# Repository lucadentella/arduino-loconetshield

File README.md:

# Loconet Shield / Interface

## Description
Interface to connect a 5V microcontroller to the Loconet bus.
Available as an Arduino shield or a stand-alone module.
A "master" version is also available, which implements power supply and bus termination.

*Interfaccia per collegare un microcontrollore a 5V al bus Loconet.
Disponibile sia come shield per Arduino che come modulo stand-alone.
E' disponibile anche una versione "master", che aggiunge le funzionalità di alimentazione e terminazione del bus.*
## Examples

In the Arduino folder, some basic sketches are provided to demonstrate the use of the interface. The [mrrwa/LocoNet](https://github.com/mrrwa/LocoNet) library is required (can be installed via Library Manager).

*Nella cartella Arduino, sono disponibili alcuni semplici sketch per dimostrare il funzionamento della interfaccia. E' richiesta la libreria [mrrwa/LocoNet](https://github.com/mrrwa/LocoNet) (può essere installata da Library Manager).*

## Documentation
- [Basic tutorial in  **English**](https://youtu.be/1dmCtpfb8J8)  (Youtube)
- [Tutorial base in  **Italiano**](https://youtu.be/m1i-pzcgra8)  (Youtube)
- [MasterInterface+Locobuffer tutorial in  **English**](https://youtu.be/BdRhHBKUpPE)  (Youtube)
- [Tutorial su InterfacciaMaster+Locobuffer in  **Italiano**](https://youtu.be/tLN5pXX8Gf4)  (Youtube)

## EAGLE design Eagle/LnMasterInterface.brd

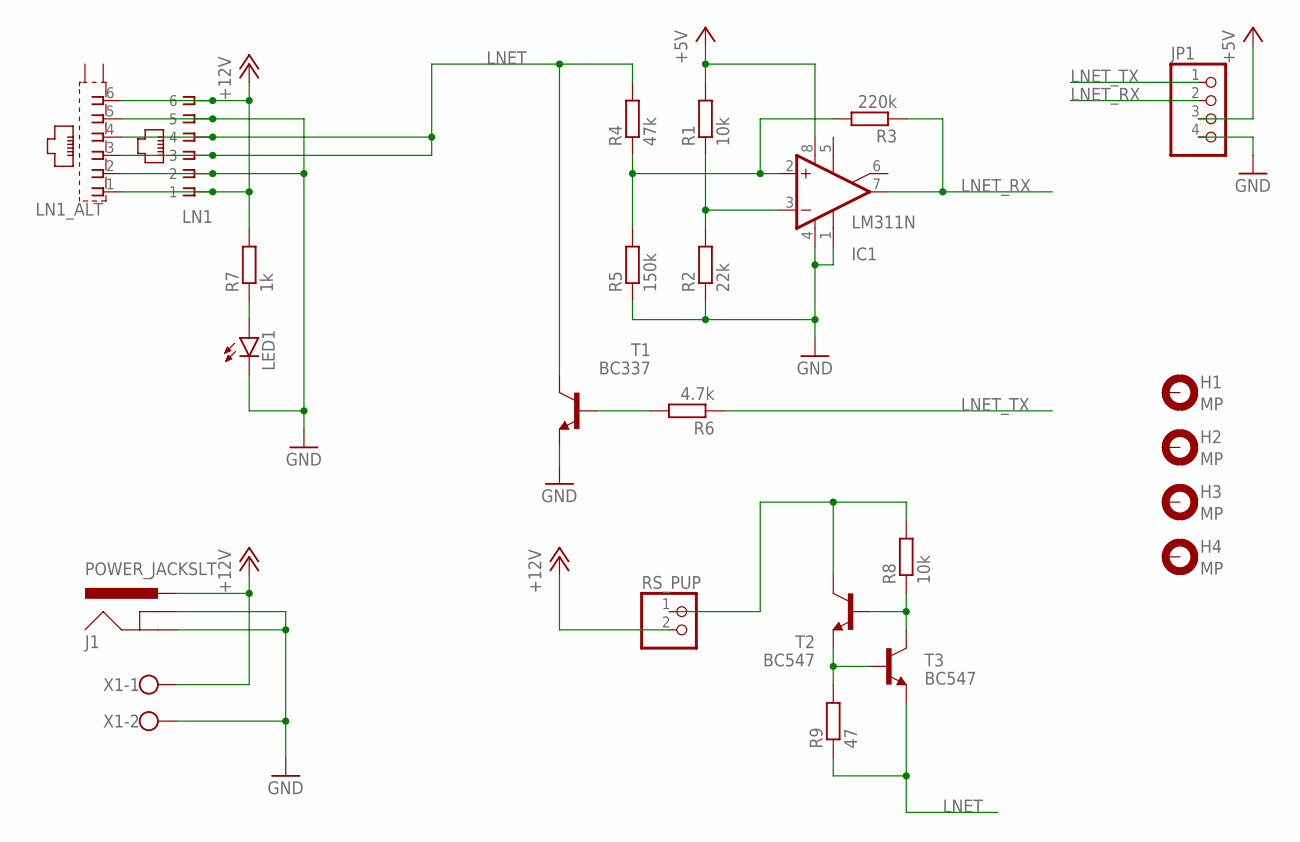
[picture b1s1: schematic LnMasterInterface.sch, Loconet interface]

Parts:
H1, H2, H3, H4: MP; 3,0-PAD
IC1: LM311N; DIL08
J1: POWER_JACKSLT; POWER_JACK_SLOT
JP1: PINHD-1X4; 1X04
LED1: LED3MM
LN1: RJ11-6X; RJ11-NO_SHIELD
LN1_ALT: YH-55-10
R1, R8: 10k; 0207/2V
R2: 22k; 0207/2V
R3: 220k; 0207/2V
R4: 47k; 0207/2V
R5: 150k; 0207/2V
R6: 4.7k; 0207/2V
R7: 1k; 0207/2V
R9: 47; 0207/2V
RS_PUP: PINHD-1X2; 1X02
T1: BC337; TO92
T2, T3: BC547; TO92
X1: W237-102

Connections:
+5V: IC1.8 (V+), JP1.3, R1.2
+12V: J1.PWR, LN1.1, LN1.6, LN1_ALT.1, LN1_ALT.6, R7.2, RS_PUP.2, X1.1
GND: IC1.1 (GND), IC1.4 (V-), J1.GND@1 (GNDBREAK), J1.GND@2 (GND), JP1.4, LED1.K (C), LN1.2, LN1.5, LN1_ALT.2, LN1_ALT.5, R2.1, R5.1, T1.1 (E), X1.2
LNET: LN1.3, LN1.4, LN1_ALT.3, LN1_ALT.4, R4.2, R9.1, T1.3 (C), T3.1 (E)
LNET_RX: IC1.7 (OUT), JP1.2, R3.1
LNET_TX: JP1.1, R6.1
unnamed: R6.2, T1.2 (B)
unnamed: LED1.A, R7.1
unnamed: IC1.3 (-IN), R1.1, R2.2
unnamed: IC1.2 (+IN), R3.2, R4.1, R5.2
unnamed: R9.2, T2.1 (E), T3.2 (B)
unnamed: R8.1, T2.2 (B), T3.3 (C)
unnamed: R8.2, RS_PUP.1, T2.3 (C)

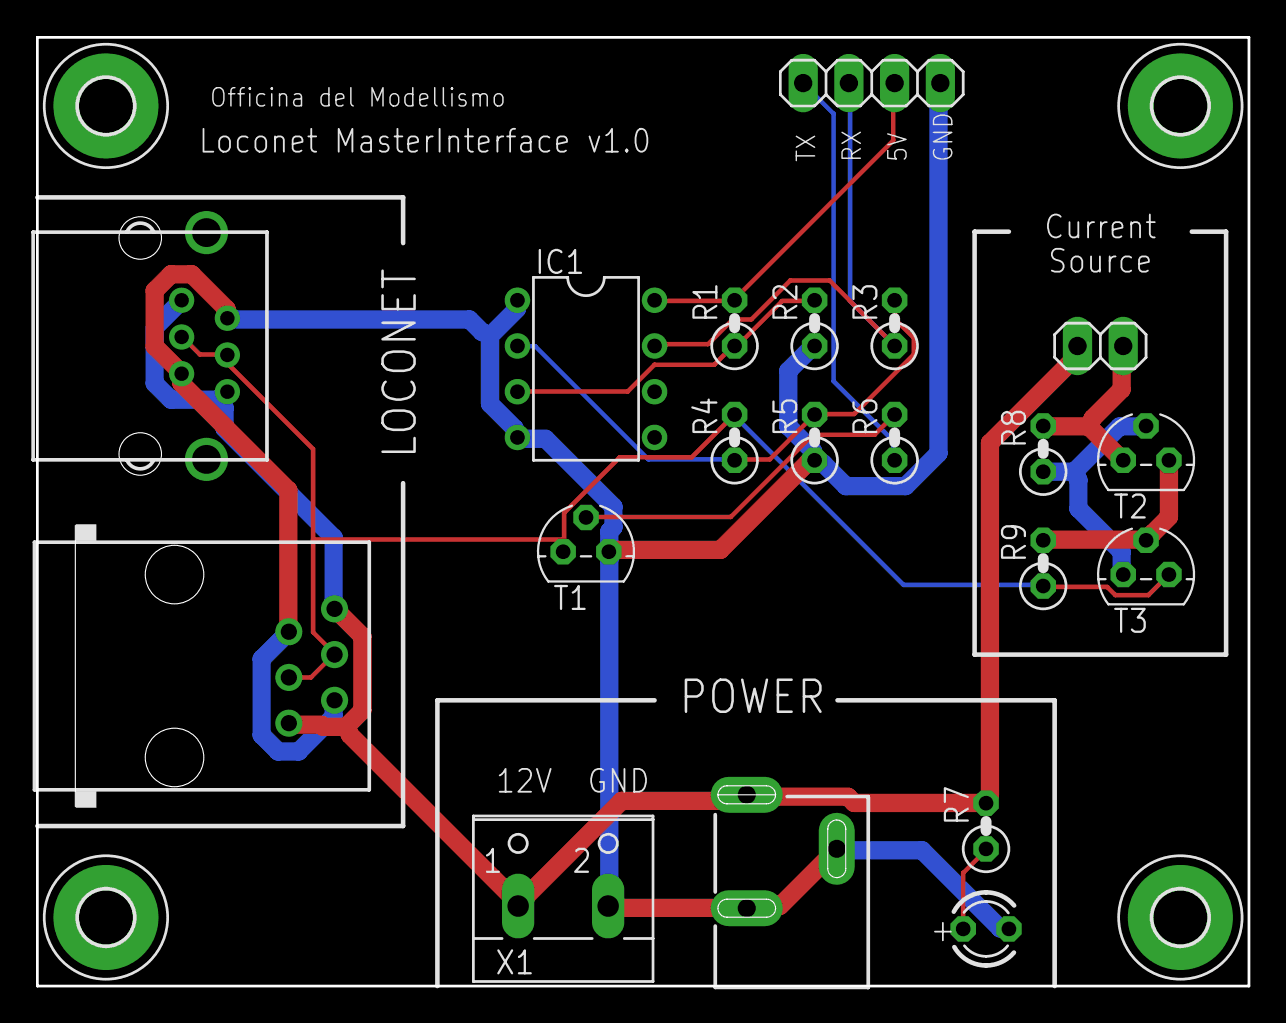
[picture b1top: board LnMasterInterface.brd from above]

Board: 2 copper layers, 67.3 x 52.7 mm, 24 parts (0 on the bottom side), 13 nets.

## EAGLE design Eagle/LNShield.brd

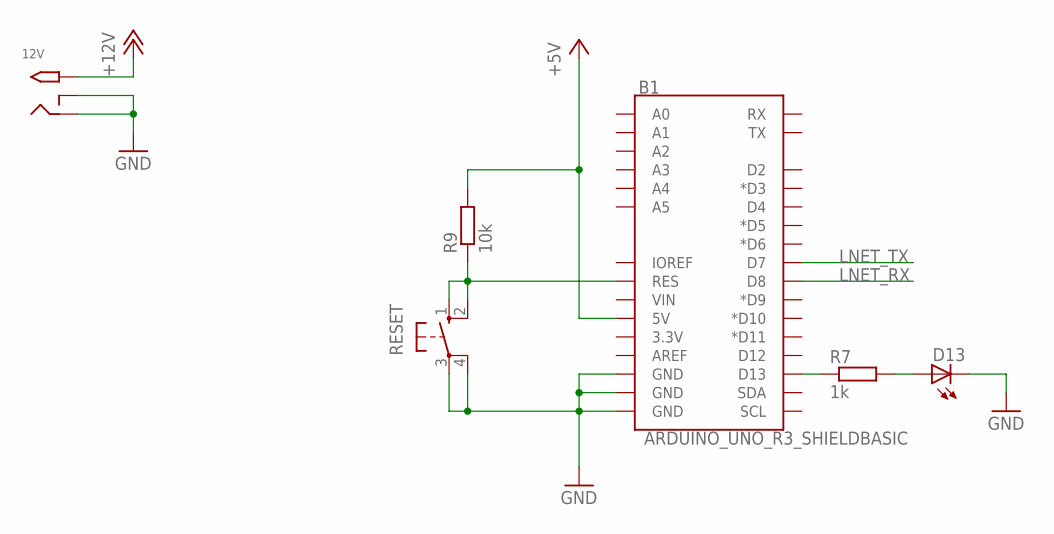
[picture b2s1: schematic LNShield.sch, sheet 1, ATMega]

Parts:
12V: 2.1MMJACKTHM; PJ-102A
B1: ARDUINO_UNO_R3_SHIELDBASIC; UNO_R3_SHIELD
D13: LED3MM
R7: 1k; 0207/2V
R9: 10k; 0207/2V
RESET: 10-XX; B3F-10XX

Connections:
+5V: B1.5V, R9.2; also elsewhere on the board
+12V: 12V.TIP; also elsewhere on the board
GND: 12V.RING, 12V.RING_SW, B1.GND@0 (GND), B1.GND@1 (GND), B1.GND@2 (GND), D13.K (C), RESET.3, RESET.4 (P1); also elsewhere on the board
LNET_RX: B1.D8; also elsewhere on the board
LNET_TX: B1.D7; also elsewhere on the board
unnamed: B1.D13, R7.1
unnamed: D13.A, R7.2
unnamed: B1.RES, R9.1, RESET.1 (S), RESET.2 (S1)

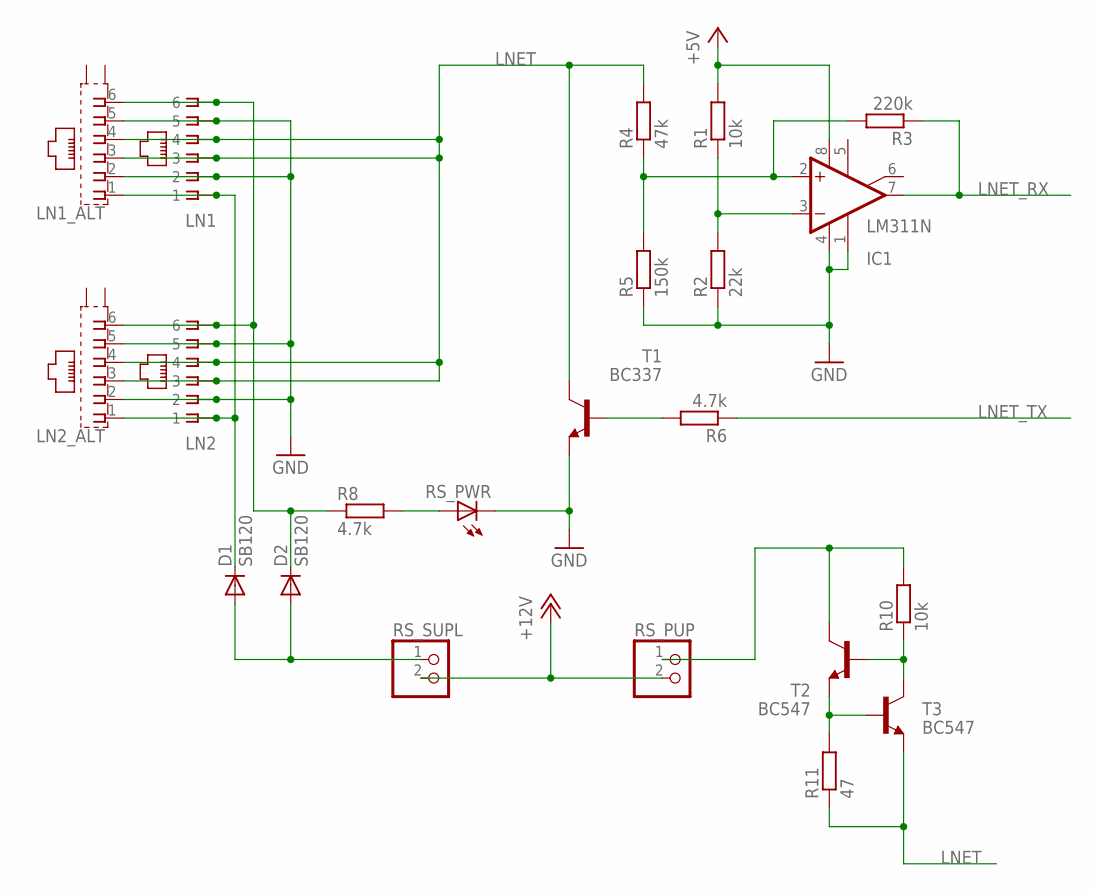
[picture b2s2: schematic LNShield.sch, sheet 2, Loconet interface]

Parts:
D1, D2: SB120; DO41-10
IC1: LM311N; DIL08
LN1, LN2: RJ11-6X; RJ11-NO_SHIELD
LN1_ALT, LN2_ALT: YH-55-10
R1, R10: 10k; 0207/2V
R2: 22k; 0207/2V
R3: 220k; 0207/2V
R4: 47k; 0207/2V
R5: 150k; 0207/2V
R6, R8: 4.7k; 0207/2V
R11: 47; 0207/2V
RS_PUP: PINHD-1X2; 1X02
RS_PWR: LED3MM
RS_SUPL: PINHD-1X2; 1X02
T1: BC337; TO92
T2, T3: BC547; TO92

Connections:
+5V: IC1.8 (V+), R1.2; also elsewhere on the board
+12V: RS_PUP.2, RS_SUPL.2; also elsewhere on the board
AA: D1.A, D2.A, RS_SUPL.1
GND: IC1.1 (GND), IC1.4 (V-), LN1.2, LN1.5, LN1_ALT.2, LN1_ALT.5, LN2.2, LN2.5, LN2_ALT.2, LN2_ALT.5, R2.1, R5.1, RS_PWR.K (C), T1.1 (E); also elsewhere on the board
LNET: LN1.3, LN1.4, LN1_ALT.3, LN1_ALT.4, LN2.3, LN2.4, LN2_ALT.3, LN2_ALT.4, R4.2, R11.1, T1.3 (C), T3.1 (E)
LNET_RX: IC1.7 (OUT), R3.1; also elsewhere on the board
LNET_TX: R6.1; also elsewhere on the board
unnamed: R6.2, T1.2 (B)
unnamed: IC1.3 (-IN), R1.1, R2.2
unnamed: IC1.2 (+IN), R3.2, R4.1, R5.2
unnamed: R11.2, T2.1 (E), T3.2 (B)
unnamed: R8.2, RS_PWR.A
unnamed: R10.1, T2.2 (B), T3.3 (C)
unnamed: R10.2, RS_PUP.1, T2.3 (C)
RAILSYNC_A: D2.C, LN1.6, LN1_ALT.6, LN2.6, LN2_ALT.6, R8.1
RAILSYNC_B: D1.C, LN1.1, LN1_ALT.1, LN2.1, LN2_ALT.1

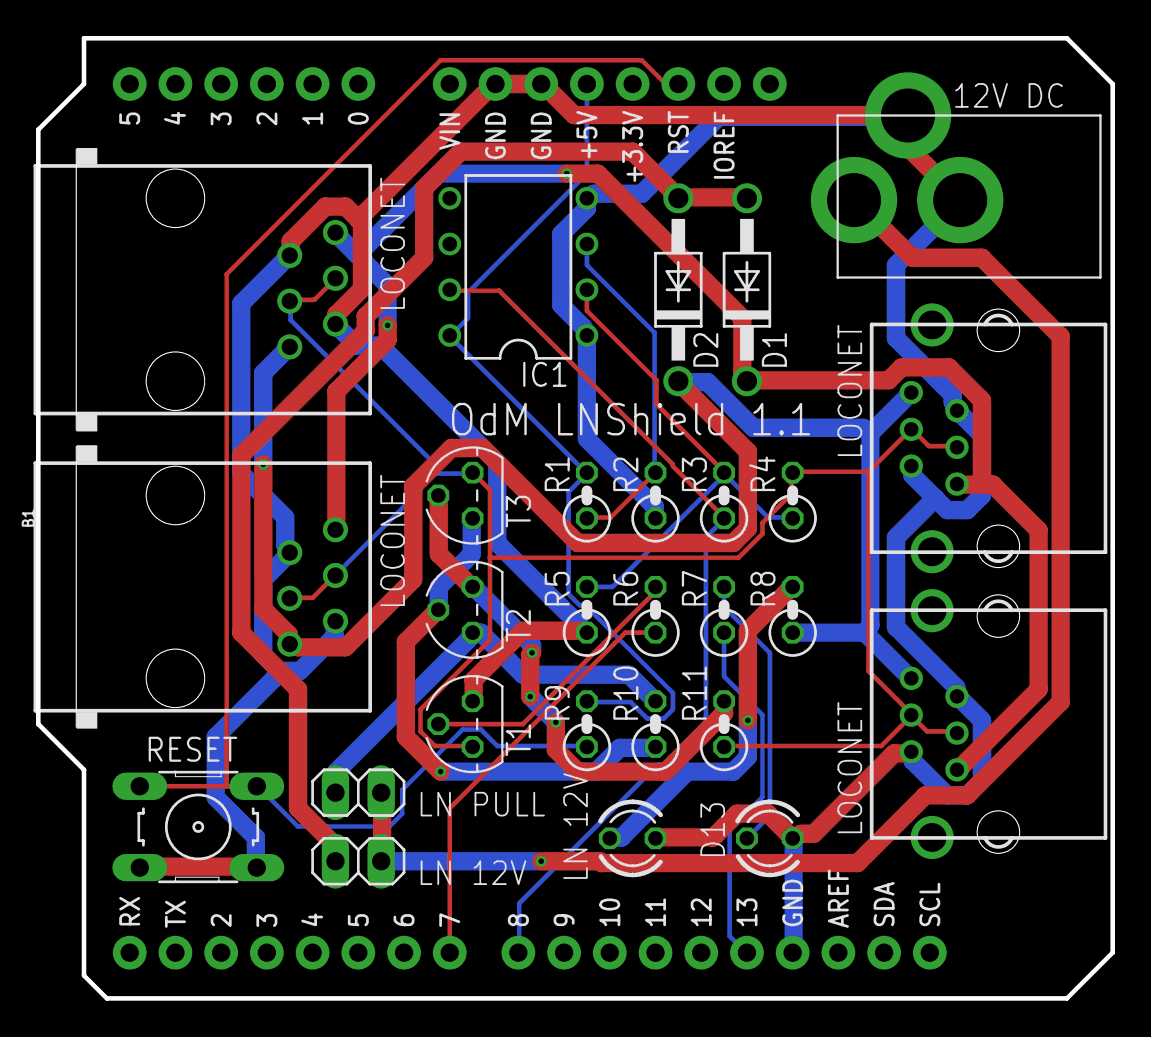
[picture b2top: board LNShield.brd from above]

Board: 2 copper layers, 59.7 x 53.3 mm, 28 parts (0 on the bottom side), 19 nets.

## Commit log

2021-02-27 Readme updated
2021-02-28 Image added
2021-02-28 Youtube links updated
2021-02-28 Link to italian tutorial fixed
2021-03-12 Sensors added
2021-03-28 Master interface and Locobuffer firmware
2021-04-12 Loconet control panel example added
2021-04-21 Schematic in PDF format added

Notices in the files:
parts and their libraries:
SparkFun-Boards: Licensing: Creative Commons ShareAlike 4.0 International - https://creativecommons.org/licenses/by-sa/4.0
